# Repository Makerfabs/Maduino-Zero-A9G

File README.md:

# Maduino-Zero-A9G

```c++
/*
Version:		V1.0
Author:			Vincent
Create Date:	2022/12/30
Note:
	
*/
```

[toc]

# Makerfabs

[Makerfabs home page](https://www.makerfabs.com/)

[Makerfabs Wiki](https://wiki.makerfabs.com/)

# Maduino-Zero-A9G
## Intruduce

Product Link ：[Maduino Zero GPRS/GPS A9G](https://www.makerfabs.com/maduino-zero-a9g.html) 

Wiki Link : [Maduino Zero A9G](https://wiki.makerfabs.com/Maduino_Zero_A9G.html) 

Maduino Zero A9G is an IoT (Internet of things) Solution based on the 32-bit Atmel’s SAMD21 MCU and GPRS/GSM GPS module A9G. It integrates a micro Controller ATSAMD21G18, GRRS/GSM GPS module A9G, which is the upgrade version of Maduino GPRS A7, power management and storage, to make the A9G ready for a real project for IoT projects such as smart-home, outdoor monitoring, etc. The Maduino Zero A9G is based on the Arduino, users can program it with Arduino IDE, which is very easy especially suit for the none-programmers. There are also guide for users to learn how to create the first IoT project with this board, with which the starters can learn the hardware and programming skill quickly. With this board, you will easy to add text, SMS, and data to your project. It is good for your smart home project or GPS tracker and so on.

## Feature

- BAT Input Voltage: 3.4-4.2V
- ATSAMD21G18, 32-Bit ARM Cortex M0+
- Micro SIM connector
- Integrated Power Control System
- Support AT Command
- Quad-Band: 850/900/1800/1900Mz
- Support GPS
- Support GPRS data traffic, the maximum data rate, download 85.6Kbps, upload 42.8Kbps

# Code

## Compiler Options

**If you have any questions，such as how to install the development board, how to download the code, how to install the library. Please refer to :[Makerfabs_FAQ](https://github.com/Makerfabs/Makerfabs_FAQ)**

- Install board : **Arduino Zero**.
- Upload codes, select **Arduino/Genuino Zero(Native USB port)**

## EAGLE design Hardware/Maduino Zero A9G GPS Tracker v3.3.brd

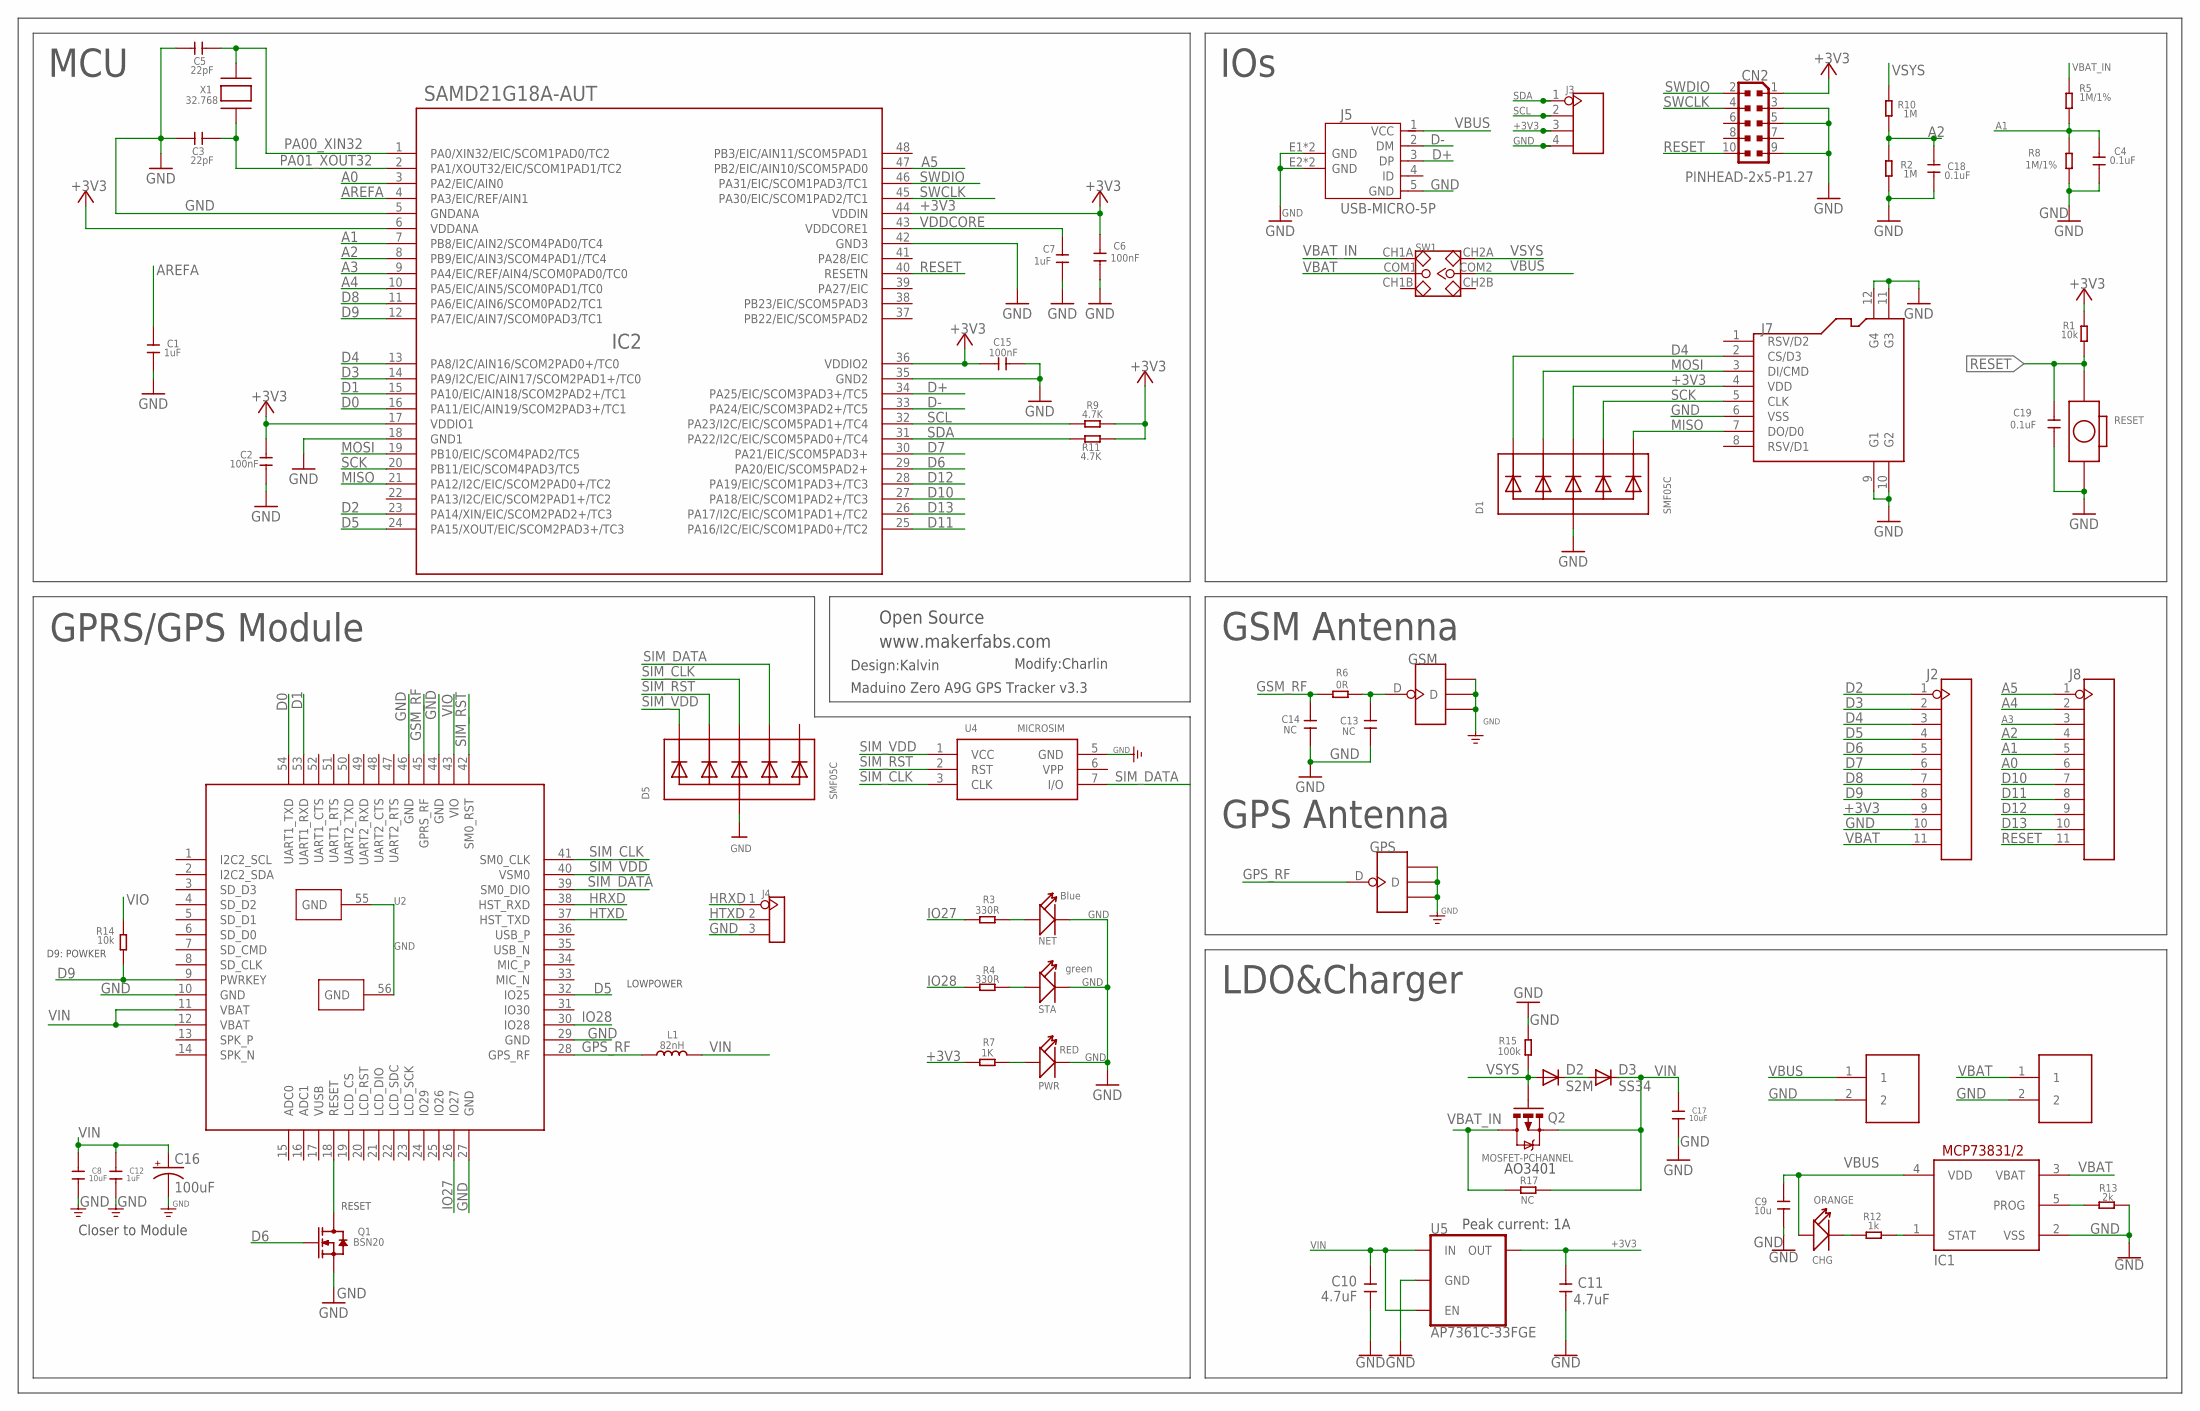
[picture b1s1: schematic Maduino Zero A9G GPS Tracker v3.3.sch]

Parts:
C1, C7, C12: 1uF; C0603
C2, C6, C15: 100nF; C0603
C3, C5: 22pF; C0603
C4, C18, C19: 0.1uF; C0603
C8, C17: 10uF; C0603
C9: 10u; C0603
C10, C11: 4.7uF; C0603
C13, C14: NC; C0402
C16: 100uF; EIA3528
CHG: ORANGE; D0603
CN2: PINHEAD-2x5-P1.27; PINHEAD_2X05_127
D1, D5: SMF05C; SOT363
D2: S2M; DO-214AC
D3: SS34; DO-214AC
GPS: ANTENNA-U-FL; 4P-U-FL
GSM: ANTENNA-U-FL; 4P-U-FL
IC1: MCP73831/OT; SOT23-5L
IC2: SAMD21G18A-AUT; TQFP48-7X7
J1, J6: PH2.0-2P-90-DIP
J2, J8: HEADER-11P-2.54; 11P-2.54
J3: HEADER-4P-60/35MILROUND; 4P-65/35ROUND
J4: HEADER-3P-2.54; 3P-2.54
J5: USB-MICRO-5P; MICRO-USB-5P
J7: HOLDER-MICROSD-8P; 8P-SMD
L1: 82nH; L0603
NET: Blue; LED-0603
PWR: RED; LED-0603
Q1: BSN20; SOT23@1
Q2: MOSFET-PCHANNEL; SOT23-3
R1, R14: 10k; R0603
R2, R10: 1M; R0603
R3, R4: 330R; R0603
R5, R8: 1M/1%; R0603
R6: 0R; R0603
R7: 1K; R0603
R9, R11: 4.7K; R0603
R12: 1k; R0603
R13: 2k; R0603
R15: 100k; R0603
R17: NC; R0603
RESET: BOTTON-2P-90D; 2P-7.62X3.56-90D
STA: green; LED-0603
SW1: SWITCH-2CH-6P; 6P-2CH-2.54-7.6X3.0
U2: A9G
U4: MICROSIM
U5: AP7361C-33FGE; 8-UDFN
X1: 32.768; XTAL3215

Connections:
+3V3: C2.2, C6.1, C11.2, C15.1, CN2.1, D1.4 (C3), IC2.6 (VDDANA), IC2.17 (VDDIO1), IC2.36 (VDDIO2), IC2.44 (VDDIN), J2.9, J3.3, J7.4 (VDD), R1.2, R7.1, R9.2, R11.2, U5.1 (OUT)
A0: IC2.3 (PA2/EIC/AIN0), J8.6
A1: C4.1, IC2.7 (PB8/EIC/AIN2/SCOM4PAD0/TC4), J8.5, R5.1, R8.2
A2: C18.1, IC2.8 (PB9/EIC/AIN3/SCOM4PAD1//TC4), J8.4, R2.2, R10.1
A3: IC2.9 (PA4/EIC/REF/AIN4/SCOM0PAD0/TC0), J8.3
A4: IC2.10 (PA5/EIC/AIN5/SCOM0PAD1/TC0), J8.2
A5: IC2.47 (PB2/EIC/AIN10/SCOM5PAD0), J8.1
AREFA: C1.1, IC2.4 (PA3/EIC/REF/AIN1)
D0: IC2.16 (PA11/EIC/AIN19/SCOM2PAD3+/TC1), U2.54 (UART1_TXD)
D1: IC2.15 (PA10/EIC/AIN18/SCOM2PAD2+/TC1), U2.53 (UART1_RXD)
D2: IC2.23 (PA14/XIN/EIC/SCOM2PAD2+/TC3), J2.1
D3: IC2.14 (PA9/I2C/EIC/AIN17/SCOM2PAD1+/TC0), J2.2
D4: D1.1 (C1), IC2.13 (PA8/I2C/AIN16/SCOM2PAD0+/TC0), J2.3, J7.2 (CS/D3)
D5: IC2.24 (PA15/XOUT/EIC/SCOM2PAD3+/TC3), J2.4, U2.32 (IO25)
D6: IC2.29 (PA20/EIC/SCOM5PAD2+), J2.5, Q1.1 (G)
D7: IC2.30 (PA21/EIC/SCOM5PAD3+), J2.6
D8: IC2.11 (PA6/EIC/AIN6/SCOM0PAD2/TC1), J2.7
D9: IC2.12 (PA7/EIC/AIN7/SCOM0PAD3/TC1), J2.8, R14.1, U2.9 (PWRKEY)
D10: IC2.27 (PA18/EIC/SCOM1PAD2+/TC3), J8.7
D11: IC2.25 (PA16/I2C/EIC/SCOM1PAD0+/TC2), J8.8
D12: IC2.28 (PA19/EIC/SCOM1PAD3+/TC3), J8.9
D13: IC2.26 (PA17/I2C/EIC/SCOM1PAD1+/TC2), J8.10
D+: IC2.34 (PA25/EIC/SCOM3PAD3+/TC5), J5.3 (DP)
D-: IC2.33 (PA24/EIC/SCOM3PAD2+/TC5), J5.2 (DM)
GND: C1.2, C2.1, C3.2, C4.2, C5.2, C6.2, C7.2, C8.1, C9.1, C10.1, C11.1, C12.1, C13.1, C14.1, C15.2, C16.C (-), C17.1, C18.2, C19.1, CN2.3, CN2.5, CN2.9, D1.2 (A), D5.2 (A), GPS.GND1, GPS.GND2, GPS.GND3, GSM.GND1, GSM.GND2, GSM.GND3, IC1.2 (VSS), IC2.5 (GNDANA), IC2.18 (GND1), IC2.35 (GND2), IC2.42 (GND3), J1.2, J2.10, J3.4, J4.3, J5.5 (GND), J5.E1 (GND), J5.E2 (GND), J5.P1 (GND), J5.P2 (GND), J6.2, J7.6 (VSS), J7.9 (G1), J7.10 (G2), J7.11 (G3), J7.12 (G4), NET.-, PWR.-, Q1.2 (S), R2.1, R8.1, R13.2, R15.2, RESET.P$2 (2), STA.-, U2.10 (GND), U2.27 (GND), U2.29 (GND), U2.44 (GND), U2.46 (GND), U2.55 (GND), U2.56 (GND), U4.5 (GND), U5.4 (GND), U5.EP (GND)
GPS_RF: GPS.D, L1.1, U2.28 (GPS_RF)
GSM_RF: C14.2, R6.1, U2.45 (GPRS_RF)
HRXD: J4.1, U2.38 (HST_RXD)
HTXD: J4.2, U2.37 (HST_TXD)
IO27: R3.1, U2.26 (IO27)
IO28: R4.1, U2.30 (IO28)
MISO: D1.6 (C5), IC2.21 (PA12/I2C/EIC/SCOM2PAD0+/TC2), J7.7 (DO/D0)
MOSI: D1.3 (C2), IC2.19 (PB10/EIC/SCOM4PAD2/TC5), J7.3 (DI/CMD)
unnamed: R4.2, STA.+
unnamed: D2.C, D3.A
unnamed: PWR.+, R7.2
unnamed: NET.+, R3.2
unnamed: Q1.3 (D), U2.18 (RESET)
unnamed: CHG.-, R12.1
unnamed: IC1.1 (STAT), R12.2
unnamed: IC1.5 (PROG), R13.1
unnamed: C13.2, GSM.D, R6.2
PA00_XIN32: C5.1, IC2.1 (PA0/XIN32/EIC/SCOM1PAD0/TC2), X1.P$2
PA01_XOUT32: C3.1, IC2.2 (PA1/XOUT32/EIC/SCOM1PAD1/TC2), X1.P$1
RESET: C19.2, CN2.10, IC2.40 (RESETN), J8.11, R1.1, RESET.P$1 (1)
SCK: D1.5 (C4), IC2.20 (PB11/EIC/SCOM4PAD3/TC5), J7.5 (CLK)
SCL: IC2.32 (PA23/I2C/EIC/SCOM5PAD1+/TC4), J3.2, R9.1
SDA: IC2.31 (PA22/I2C/EIC/SCOM5PAD0+/TC4), J3.1, R11.1
SIM_CLK: D5.4 (C3), U2.41 (SM0_CLK), U4.3 (CLK)
SIM_DATA: D5.5 (C4), U2.39 (SM0_DIO), U4.7 (I/O)
SIM_RST: D5.3 (C2), U2.42 (SM0_RST), U4.2 (RST)
SIM_VDD: D5.1 (C1), U2.40 (VSM0), U4.1 (VCC)
SWCLK: CN2.4, IC2.45 (PA30/EIC/SCOM1PAD2/TC1)
SWDIO: CN2.2, IC2.46 (PA31/EIC/SCOM1PAD3/TC1)
VBAT: IC1.3 (VBAT), J2.11, J6.1, SW1.COM1
VBAT_IN: Q2.3 (D), R5.2, R17.1, SW1.CH1A
VBUS: C9.2, CHG.+, IC1.4 (VDD), J1.1, J5.1 (VCC), SW1.COM2
VDDCORE: C7.1, IC2.43 (VDDCORE1)
VIN: C8.2, C10.2, C12.2, C16.A (+), C17.2, D3.C, L1.2, Q2.2 (S), R17.2, U2.11 (VBAT), U2.12 (VBAT), U5.5 (EN), U5.8 (IN)
VIO: R14.2, U2.43 (VIO)
VSYS: D2.A, Q2.1 (G), R10.2, R15.1, SW1.CH2A

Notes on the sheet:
GSM Antenna
GPRS/GPS Module
LOWPOWER
RESET
D9: POWKER
Peak current: 1A
www.makerfabs.com
MCU
IOs
LDO&Charger
GPS Antenna
Design:Kalvin
Modify:Charlin
Open Source
Closer to Module
AO3401
Maduino Zero A9G GPS Tracker v3.3

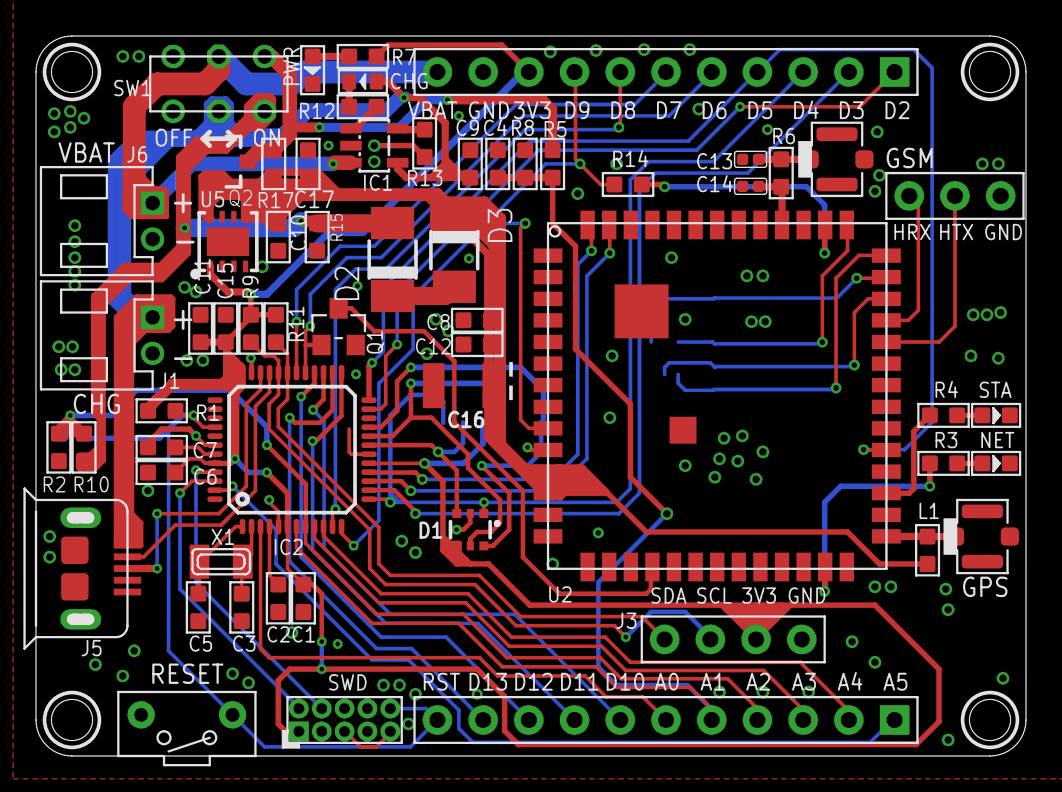
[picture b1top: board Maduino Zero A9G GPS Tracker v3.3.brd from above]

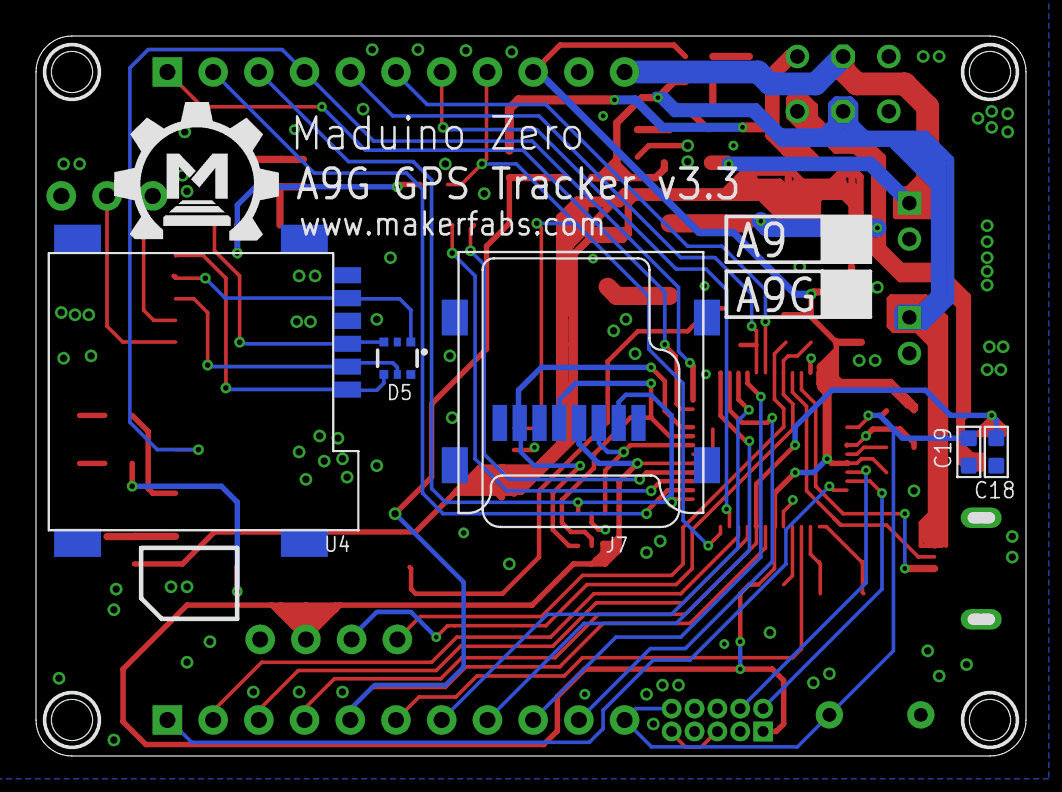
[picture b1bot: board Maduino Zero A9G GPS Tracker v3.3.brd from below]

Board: 2 copper layers, 55.0 x 40.0 mm, 66 parts (6 on the bottom side), 61 nets.

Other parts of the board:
U$1: MAKERFABS_0.3

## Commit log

2019-11-26 v1.0
    view the teperature and humidity on the internet
2019-11-26 v1.0
    input AT commands via serial monitor to learn how to use A9/A9G module
2019-11-26 v1.0
    show the temperature and humidity on OLED
2020-02-29 v1.0
    Get GPS location from A9G
2020-02-29 v1.0
    Send message to the board to control LED
2021-05-27 Hardware
    add hardware
2021-07-06 Create A9G_SD
2022-09-22 Fix bug
2022-12-30 Edit readme

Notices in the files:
parts and their libraries:
microbuilder: This work is placed in the public domain, and may be freely used for commercial and non-commercial work with the following conditions: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
SparkFun-Capacitors: Licensing: Creative Commons ShareAlike 4.0 International - https://creativecommons.org/licenses/by-sa/4.0
